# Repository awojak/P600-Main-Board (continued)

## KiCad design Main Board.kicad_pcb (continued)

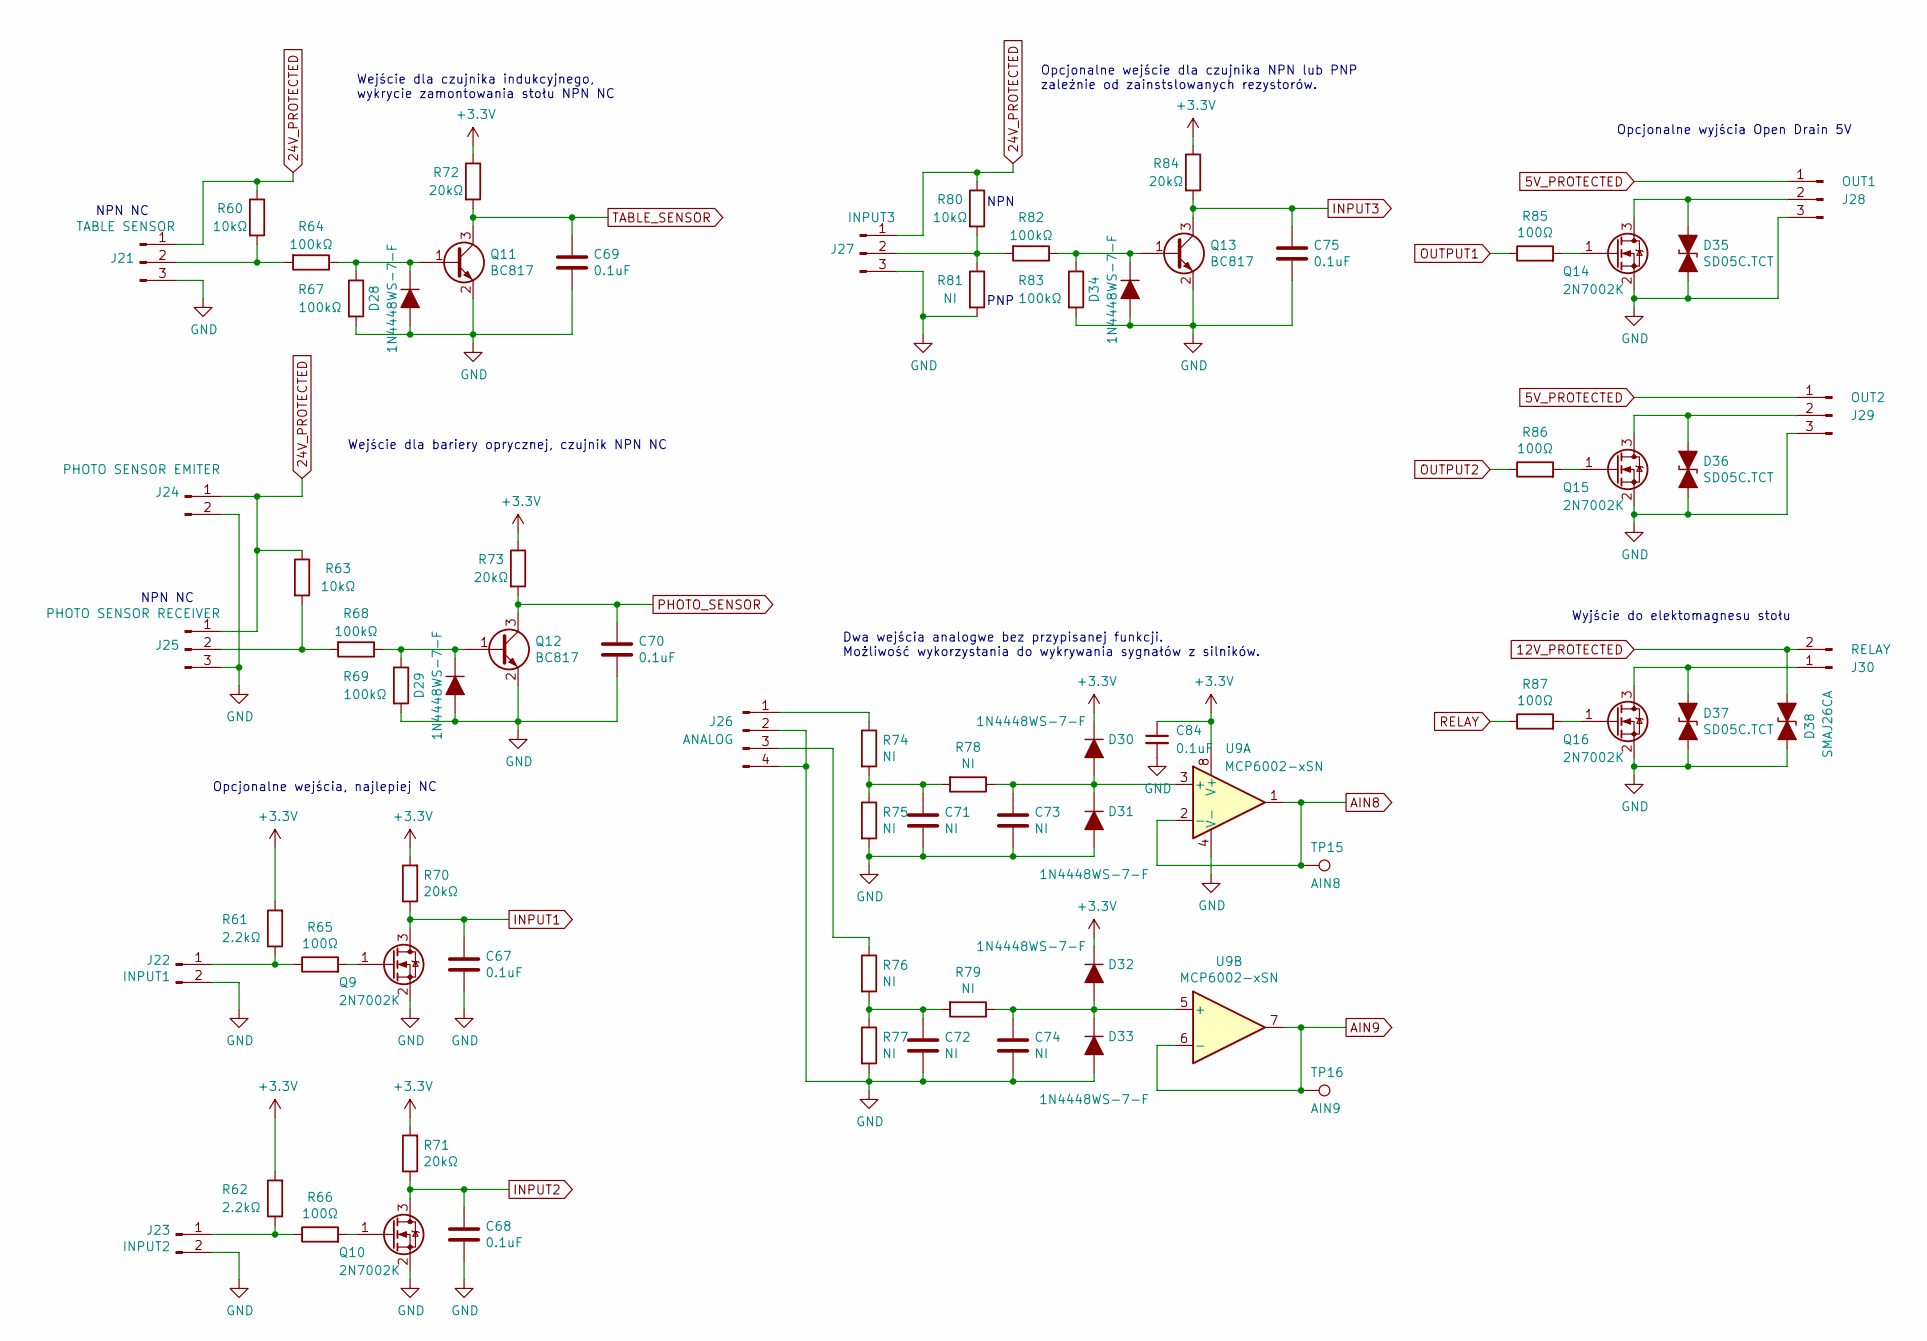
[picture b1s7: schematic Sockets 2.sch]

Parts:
C67, C68, C69, C70, C75: 0.1uF; C_0603_1608Metric
C71, C72, C73, C74: NI; C_0603_1608Metric
C84: 0.1uF; C_0603_1608Metric; Tolerancja 10%
D28, D29, D30, D31, D32, D33, D34: 1N4448WS-7-F; D_SOD-323
D35, D36, D37: SD05C.TCT; D_SOD-323
D38: SMAJ26CA; D_SMA
J21: TABLE SENSOR; JST_PH_B3B-PH-K_1x03_P2.00mm_Vertical
J22: INPUT1; JST_PH_B2B-PH-K_1x02_P2.00mm_Vertical
J23: INPUT2; JST_PH_B2B-PH-K_1x02_P2.00mm_Vertical
J24: PHOTO SENSOR EMITER; JST_PH_B2B-PH-K_1x02_P2.00mm_Vertical
J25: PHOTO SENSOR RECEIVER; JST_PH_B3B-PH-K_1x03_P2.00mm_Vertical
J26: ANALOG; JST_PH_B4B-PH-K_1x04_P2.00mm_Vertical
J27: INPUT3; JST_PH_B3B-PH-K_1x03_P2.00mm_Vertical
J28: OUT1; JST_PH_B3B-PH-K_1x03_P2.00mm_Vertical
J29: OUT2; JST_PH_B3B-PH-K_1x03_P2.00mm_Vertical
J30: RELAY; JST_PH_B2B-PH-K_1x02_P2.00mm_Vertical
Q9, Q10, Q14, Q15, Q16: 2N7002K; SOT-23
Q11, Q12, Q13: BC817; SOT-23
R60, R63, R80: 10kΩ; R_0603_1608Metric
R61, R62: 2.2kΩ; R_0603_1608Metric
R64, R67, R68, R69, R82, R83: 100kΩ; R_0603_1608Metric
R65, R66, R85, R86, R87: 100Ω; R_0603_1608Metric
R70, R71, R72, R73, R84: 20kΩ; R_0603_1608Metric
R74, R75, R76, R77, R78, R79, R81: NI; R_0603_1608Metric
TP15: AIN8; TestPoint_Pad_D1.5mm
TP16: AIN9; TestPoint_Pad_D1.5mm
U9: MCP6002-xSN; SOIC-8_3.9x4.9mm_P1.27mm

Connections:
5V_PROTECTED: J28.1, J29.1; also elsewhere on the board
12V_PROTECTED: D38.1 (A1), J30.2; also elsewhere on the board
24V_PROTECTED: J21.1, J24.1, J25.1, J27.1, R60.1, R63.1, R80.1; also elsewhere on the board
+3V3: C84.1, D30.1 (K), D32.1 (K), R61.2, R62.2, R70.2, R71.2, R72.1, R73.1, R84.1, U9.8 (V+); also elsewhere on the board
AIN8: TP15.1, U9.1, U9.2 (-); also elsewhere on the board
AIN9: TP16.1, U9.6 (-), U9.7; also elsewhere on the board
GND: C67.2, C68.2, C69.2, C70.2, C71.2, C72.2, C73.2, C74.2, C75.2, C84.2, D28.2 (A), D29.2 (A), D31.2 (A), D33.2 (A), D34.2 (A), D35.2 (A2), D36.2 (A2), D37.2 (A2), D38.2 (A2), J21.3, J22.2, J23.2, J24.2, J25.3, J26.2, J26.4, J27.3, J28.3, J29.3, Q9.2 (S), Q10.2 (S), Q11.2 (E), Q12.2 (E), Q13.2 (E), Q14.2 (S), Q15.2 (S), Q16.2 (S), R67.2, R69.2, R75.2, R77.2, R81.2, R83.2, U9.4 (V-); also elsewhere on the board
INPUT1: C67.1, Q9.3 (D), R70.1; also elsewhere on the board
INPUT2: C68.1, Q10.3 (D), R71.1; also elsewhere on the board
INPUT3: C75.1, Q13.3 (C), R84.2; also elsewhere on the board
unnamed: C71.1, R74.2, R75.1, R78.2
unnamed: C72.1, R76.2, R77.1, R79.2
unnamed: C73.1, D30.2 (A), D31.1 (K), R78.1, U9.3 (+)
unnamed: C74.1, D32.2 (A), D33.1 (K), R79.1, U9.5 (+)
unnamed: D28.1 (K), Q11.1 (B), R64.1, R67.1
unnamed: D29.1 (K), Q12.1 (B), R68.1, R69.1
unnamed: D34.1 (K), Q13.1 (B), R82.1, R83.1
unnamed: D35.1 (A1), J28.2, Q14.3 (D)
unnamed: D36.1 (A1), J29.2, Q15.3 (D)
unnamed: D37.1 (A1), J30.1, Q16.3 (D)
unnamed: J21.2, R60.2, R64.2
unnamed: J22.1, R61.1, R65.1
unnamed: J23.1, R62.1, R66.1
unnamed: J25.2, R63.2, R68.2
unnamed: J26.1, R74.1
unnamed: J26.3, R76.1
unnamed: J27.2, R80.2, R81.1, R82.2
unnamed: Q9.1 (G), R65.2
unnamed: Q10.1 (G), R66.2
unnamed: Q14.1 (G), R85.2
unnamed: Q15.1 (G), R86.2
unnamed: Q16.1 (G), R87.2
OUTPUT1: R85.1; also elsewhere on the board
OUTPUT2: R86.1; also elsewhere on the board
PHOTO_SENSOR: C70.1, Q12.3 (C), R73.2; also elsewhere on the board
RELAY: R87.1; also elsewhere on the board
TABLE_SENSOR: C69.1, Q11.3 (C), R72.2; also elsewhere on the board

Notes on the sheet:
NPN NC
NPN
PNP
Dwa wejścia analogwe bez przypisanej funkcji. Możliwość wykorzystania do wykrywania sygnałów z silników.
Wejście dla bariery oprycznej, czujnik NPN NC
Wejście dla czujnika indukcyjnego, wykrycie zamontowania stołu NPN NC
Opcjonalne wejście dla czujnika NPN lub PNP zależnie od zainstslowanych rezystorów.
Opcjonalne wyjścia Open Drain 5V
Wyjście do elektomagnesu stołu
Opcjonalne wejścia, najlepiej NC

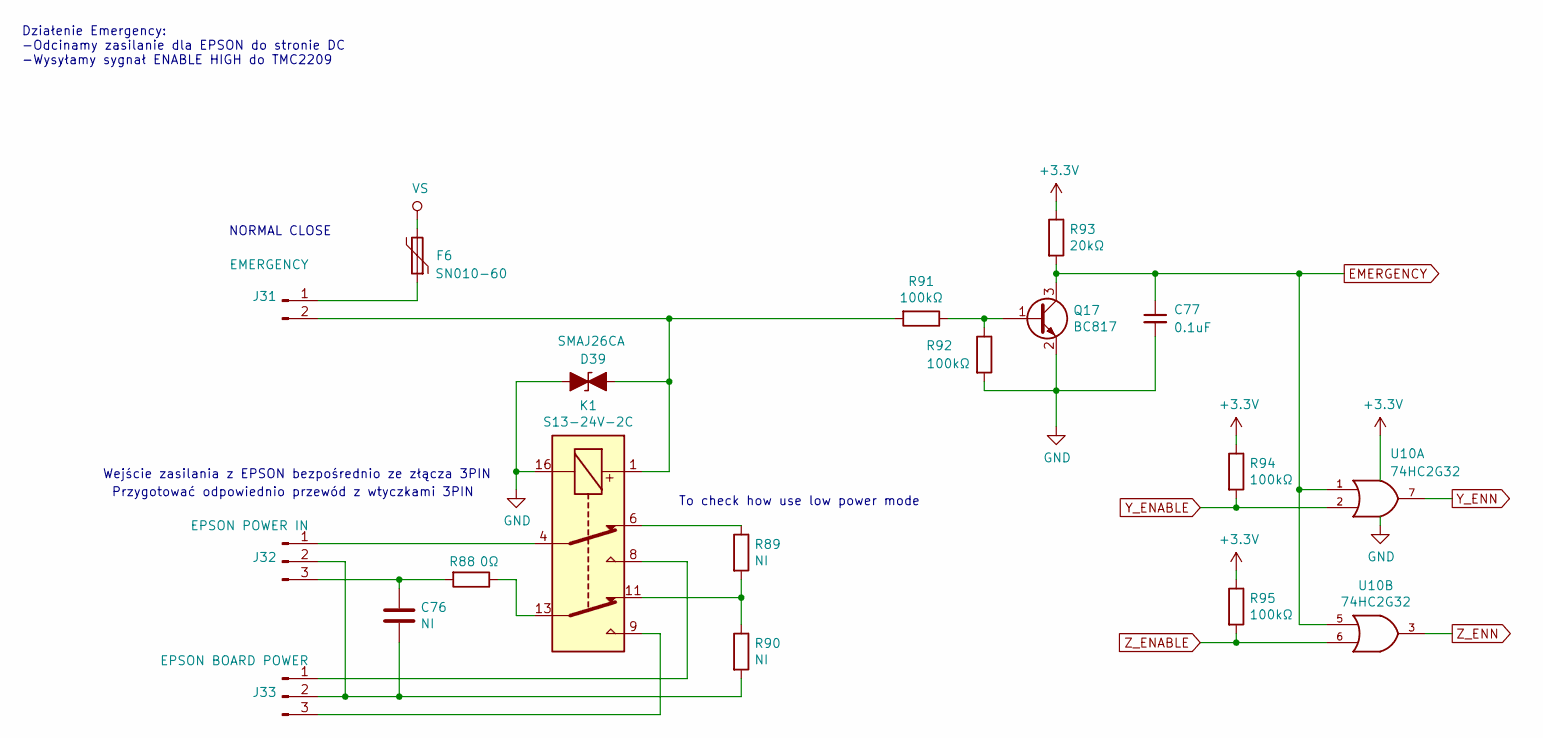
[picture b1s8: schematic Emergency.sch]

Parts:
C76: NI; C_0805_2012Metric
C77: 0.1uF; C_0603_1608Metric
D39: SMAJ26CA; D_SMA
F6: SN010-60; Fuse_1206_3216Metric
J31: EMERGENCY; JST_PH_B2B-PH-K_1x02_P2.00mm_Vertical
J32: EPSON POWER IN; JST_PH_B3B-PH-K_1x03_P2.00mm_Vertical
J33: EPSON BOARD POWER; JST_PH_B3B-PH-K_1x03_P2.00mm_Vertical
K1: S13-24V-2C; Relay_DPDT_Omron_G5V-2
Q17: BC817; SOT-23
R88: 0Ω; R_0805_2012Metric
R89, R90: NI; R_0805_2012Metric
R91, R92, R94, R95: 100kΩ; R_0603_1608Metric
R93: 20kΩ; R_0603_1608Metric
U10: 74HC2G32; VSSOP-8_2.3x2mm_P0.5mm

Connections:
+3V3: R93.1, R94.1, R95.1, U10.8 (VCC); also elsewhere on the board
EMERGENCY: C77.1, Q17.3 (C), R93.2, U10.1, U10.5; also elsewhere on the board
GND: C77.2, D39.1 (A1), K1.16, Q17.2 (E), R92.2, U10.4 (GND); also elsewhere on the board
unnamed: C76.1, J32.3, R88.2
unnamed: C76.2, J32.2, J33.2, R90.2
unnamed: D39.2 (A2), J31.2, K1.1, R91.2
unnamed: F6.1, J31.1
unnamed: J32.1, K1.4
unnamed: J33.1, K1.8
unnamed: J33.3, K1.9
unnamed: K1.6, R89.1
unnamed: K1.11, R89.2, R90.1
unnamed: K1.13, R88.1
unnamed: Q17.1 (B), R91.1, R92.1
VS: F6.2; also elsewhere on the board
Y_ENABLE: R94.2, U10.2; also elsewhere on the board
Y_ENN: U10.7; also elsewhere on the board
Z_ENABLE: R95.2, U10.6; also elsewhere on the board
Z_ENN: U10.3; also elsewhere on the board

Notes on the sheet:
Działenie Emergency: -Odcinamy zasilanie dla EPSON do stronie DC -Wysyłamy sygnał ENABLE HIGH do TMC2209
Wejście zasilania z EPSON bezpośrednio ze złącza 3PIN
Przygotować odpowiednio przewód z wtyczkami 3PIN
NORMAL CLOSE
To check how use low power mode

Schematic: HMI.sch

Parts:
C78: 0.1uF; C_0603_1608Metric; Tolerancja 10%
C79, C80, C81, C82: 0.1uF; C_0603_1608Metric
C85, C86: 0.01uF; C_0603_1608Metric
D40, D41, D42, D43: SKL32; D_SOD-123F
D44, D45: SD05C.TCT; D_SOD-323
F7: SR050; Fuse_0805_2012Metric
J34: Display; JST_PH_B10B-PH-K_1x10_P2.00mm_Vertical
J35: SPI Interface; JST_PH_B5B-PH-K_1x05_P2.00mm_Vertical
J36: I2C Interface; JST_PH_B4B-PH-K_1x04_P2.00mm_Vertical
J37: LED4; JST_PH_B2B-PH-K_1x02_P2.00mm_Vertical
J38: LED3; JST_PH_B2B-PH-K_1x02_P2.00mm_Vertical
J39: Key 3; JST_PH_B2B-PH-K_1x02_P2.00mm_Vertical
J40: Key 4; JST_PH_B2B-PH-K_1x02_P2.00mm_Vertical
J41: Key 1; JST_PH_B2B-PH-K_1x02_P2.00mm_Vertical
J42: Key 2; JST_PH_B2B-PH-K_1x02_P2.00mm_Vertical
J43: Encoder; JST_PH_B3B-PH-K_1x03_P2.00mm_Vertical
Q18, Q19: 2N7002K; SOT-23
R47, R100, R101: 330Ω; R_0603_1608Metric
R96, R97: 20Ω; R_0603_1608Metric
R98, R99: 100Ω; R_0603_1608Metric
R102, R103, R104, R105, R106, R107, R108, R109, R117, R118, R119, R120: 10kΩ; R_0603_1608Metric
RN3, RN4: 330Ω; R_Array_Convex_4x0603
U11: 74HC245; TSSOP-20_4.4x6.5mm_P0.65mm

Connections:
3.3V_PROTECTED: J36.1; also elsewhere on the board
+3V3: D40.1 (K), D42.1 (K); also elsewhere on the board
+5V: C78.1, F7.2, R100.2, R101.2, R102.2, R103.2, R104.2, R105.2, R117.2, R118.2, U11.1 (A->B), U11.20 (VCC); also elsewhere on the board
ENC2_A: C85.1, R119.1; also elsewhere on the board
ENC2_B: C86.1, R120.1; also elsewhere on the board
GND: C78.2, C79.2, C80.2, C81.2, C82.2, C85.2, C86.2, D41.2 (A), D43.2 (A), D44.2 (A2), D45.2 (A2), J34.9, J34.10, J35.5, J36.3, J39.2, J40.2, J41.2, J42.2, J43.2, Q18.2 (S), Q19.2 (S), U11.10 (GND), U11.19 (CE); also elsewhere on the board
I2C_SCL: D40.2 (A), D41.1 (K), R97.2; also elsewhere on the board
I2C_SDA: D42.2 (A), D43.1 (K), R96.2; also elsewhere on the board
KEY_1: C81.1, R108.1; also elsewhere on the board
KEY_2: C82.1, R109.1; also elsewhere on the board
KEY_3: C79.1, R106.1; also elsewhere on the board
KEY_4: C80.1, R107.1; also elsewhere on the board
LCD_DB4: U11.7 (A5); also elsewhere on the board
LCD_DB5: U11.6 (A4); also elsewhere on the board
LCD_DB6: U11.5 (A3); also elsewhere on the board
LCD_DB7: U11.4 (A2); also elsewhere on the board
LCD_E: U11.3 (A1); also elsewhere on the board
LCD_PWM: U11.8 (A6); also elsewhere on the board
LCD_RS: U11.2 (A0); also elsewhere on the board
LED3: R98.1; also elsewhere on the board
LED4: R99.1; also elsewhere on the board
unnamed: D44.1 (A1), J37.2, Q19.3 (D)
unnamed: D45.1 (A1), J38.2, Q18.3 (D)
unnamed: F7.1, J34.1, J35.1
unnamed: J34.2, RN3.4 (R4.1)
unnamed: J34.3, RN3.3 (R3.1)
unnamed: J34.4, RN3.2 (R2.1)
unnamed: J34.5, RN3.1 (R1.1)
unnamed: J34.6, RN4.4 (R4.1)
unnamed: J34.7, RN4.3 (R3.1)
unnamed: J34.8, RN4.2 (R2.1)
unnamed: J35.4, R47.2
unnamed: J36.2, R96.1
unnamed: J36.4, R97.1
unnamed: J37.1, R101.1
unnamed: J38.1, R100.1
unnamed: J39.1, R102.1, R106.2
unnamed: J40.1, R103.1, R107.2
unnamed: J41.1, R104.1, R108.2
unnamed: J42.1, R105.1, R109.2
unnamed: J43.1, R117.1, R119.2
unnamed: J43.3, R118.1, R120.2
unnamed: Q18.1 (G), R98.2
unnamed: Q19.1 (G), R99.2
unnamed: RN3.5 (R4.2), U11.18 (B0)
unnamed: RN3.6 (R3.2), U11.17 (B1)
unnamed: RN3.7 (R2.2), U11.16 (B2)
unnamed: RN3.8 (R1.2), U11.15 (B3)
unnamed: RN4.5 (R4.2), U11.14 (B4)
unnamed: RN4.6 (R3.2), U11.13 (B5)
unnamed: RN4.7 (R2.2), U11.12 (B6)
SPI_MISO: R47.1; also elsewhere on the board
SPI_MOSI_BUF: J35.2; also elsewhere on the board
SPI_SCLK_BUF: J35.3; also elsewhere on the board

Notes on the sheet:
Wyjście dla Wyświetlacza HD44780
Buffered outputs signals
Złącza JST PH
Wejścia dla klawiszy funkcyjnych, nie przypisane
RC Debounce
Check if switching is fast enought
ESD
Wyjście I2C do potencjanych czujników
Wyjście SPI do modułu komunikacji z użytkownikiem
Wyjście OD dla opcjonalnych LED
Rotary encoder input

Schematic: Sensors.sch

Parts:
C83, C95: 0.1uF; C_0603_1608Metric; Tolerancja 10%
Q20, Q21: 2N7002K; SOT-23
R1: 10kΩ; R_0603_1608Metric
R110, R112: 2.2kΩ; R_0603_1608Metric
R111: 0Ω; R_0603_1608Metric
R113, R114: 100Ω; R_0603_1608Metric
R115, R116: 20kΩ; R_0603_1608Metric
U12: SHTC3; DFN-4-1EP_2x2mm_P1mm_EP0.7x1.6mm
U13: M24C02-WDW; TSSOP-8_4.4x3mm_P0.65mm

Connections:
5V_DETECT: Q20.3 (D), R115.1; also elsewhere on the board
12V_DETECT: Q21.3 (D), R116.1; also elsewhere on the board
+3V3: C83.1, C95.2, R1.1, R110.1, R112.1, R115.2, R116.2, U12.1 (VDD), U13.8 (VCC); also elsewhere on the board
+5V: R113.1; also elsewhere on the board
+12V: R114.1; also elsewhere on the board
EEPROM_P: R1.2, U13.7 (~WC); also elsewhere on the board
GND: C83.2, C95.1, Q20.2 (S), Q21.2 (S), U12.4 (VSS), U13.4 (VSS); also elsewhere on the board
I2C_SCL: R112.2, U12.2 (SCL), U13.6 (SCL); also elsewhere on the board
I2C_SDA: R110.2, R111.1, U13.5 (SDA); also elsewhere on the board
unnamed: Q20.1 (G), R113.2
unnamed: Q21.1 (G), R114.2
unnamed: R111.2, U12.3 (SDA)

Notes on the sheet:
Wykrycie napięć z przetwornic 5V i 12V
Czujnik wilgotności i temperatury
Rezystor do odłączenia układy gdy chcielibyśmy podłączyć taki sam na zewnętrznych I2C. I2C z wyjściem jest dzielone z tym czujnikiem

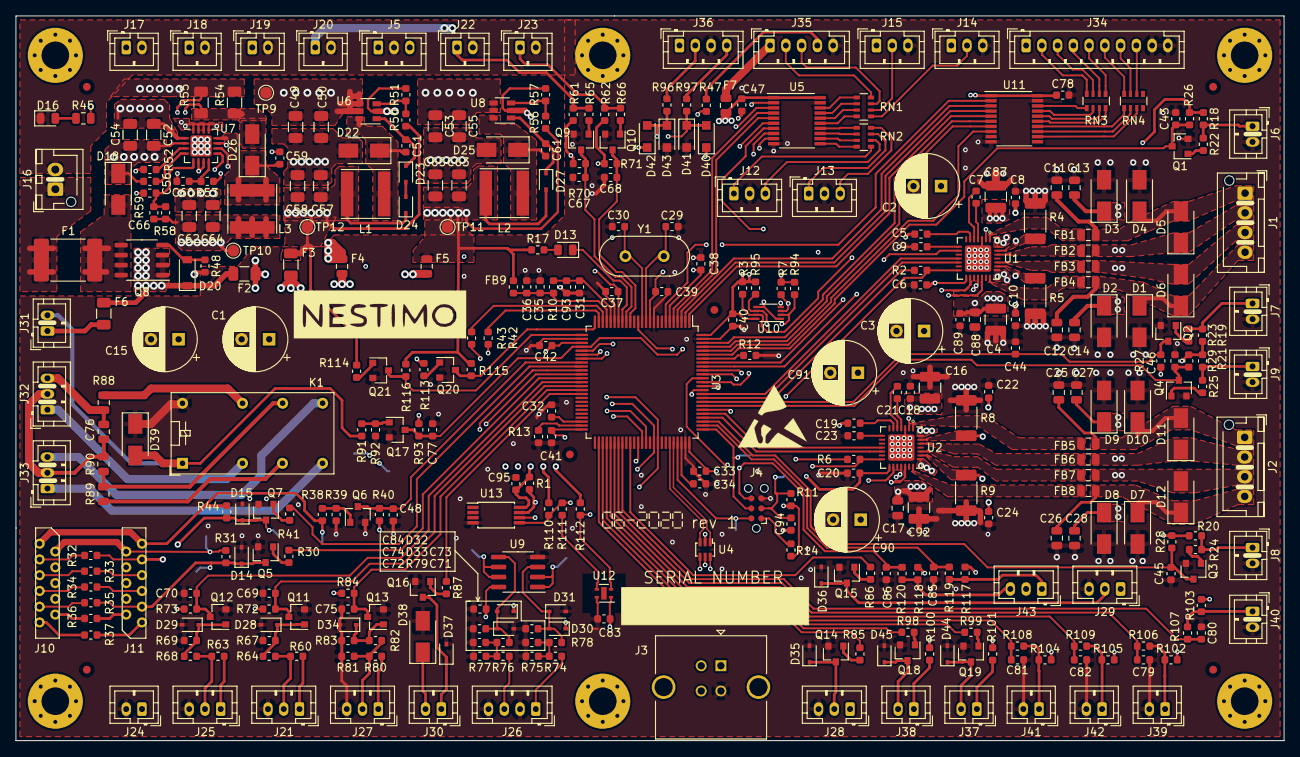
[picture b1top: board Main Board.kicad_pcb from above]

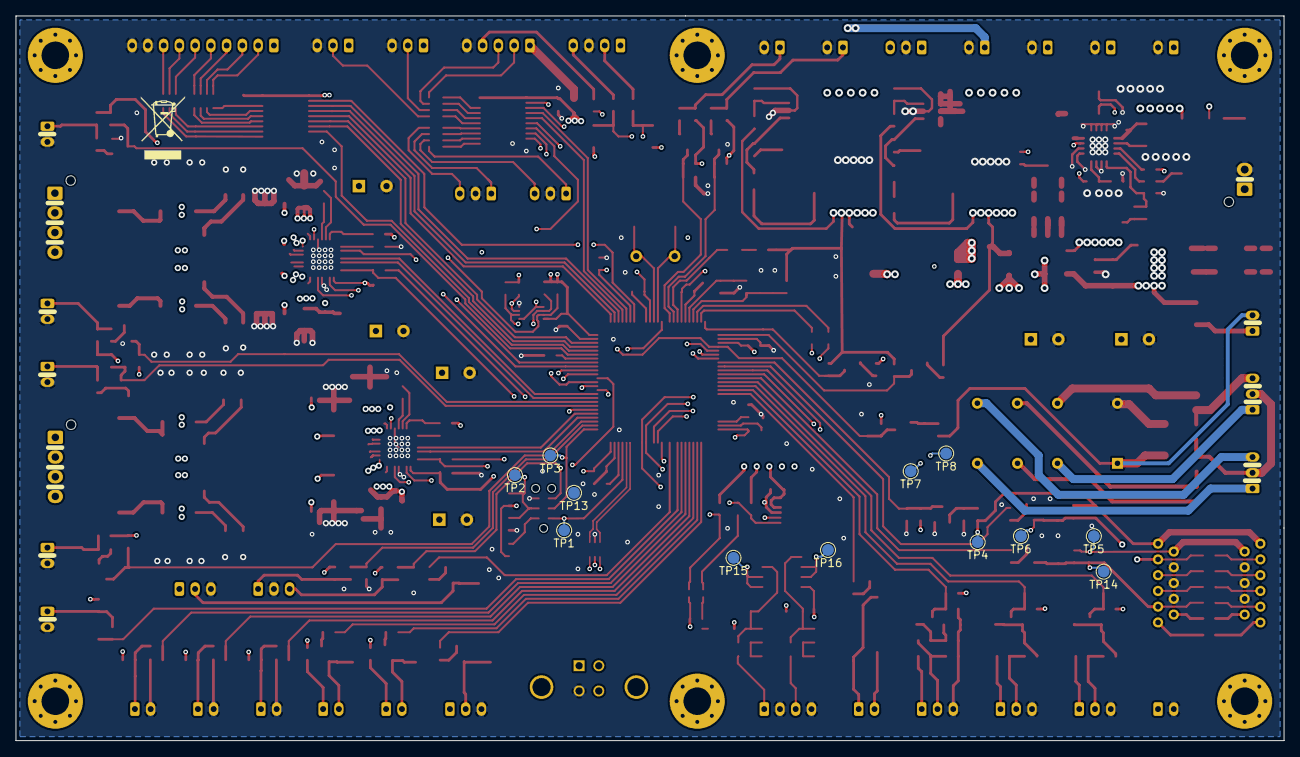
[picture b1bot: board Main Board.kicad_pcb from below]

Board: 4 copper layers, 161.0 x 92.0 mm, 383 parts (12 on the bottom side), 241 nets.

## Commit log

2019-12-04 Init Commit
2019-12-20 Added stm32f401
2019-12-22 Finished TMC2209 schematic for Y and Z motor, added BOM
2020-01-02 Added Power.sch and update BOM
2020-01-02 Finished Power Managment
2020-01-03 Added Input Limit Switch
2020-01-05 Finished Emergency Circuit
2020-01-06 Added Polyfuses and replace diodes
2020-01-06 Added USB B socket with ESD filter
2020-01-07 Added SWD and Debug out
2020-01-07 Improve schematics add new elements
2020-01-08 Numbering and finishing the schematic
2020-01-08 Shematic almost finished, BOM in KiCad 3/4 finished
2020-01-09 BOM in KiCad almost finished, genereated NETLIST, create PCB
2020-01-09 Generated BOM
2020-01-09 Improve Emergency, Added TVS diodes
2020-01-10 Update USBUF02W6
2020-01-10 Added 12V regulator, aditional input, outputs, improved inputs ESD
2020-01-11 Added analog input
2020-01-11 Improve ESD Protection for TMC2209, Fuses. Schematic ready v1
2020-01-11 Dodano brakujący footprint dla R1
2020-01-12 Routing of the power supplies are finished
2020-01-12 Rozmieszczenie elementów, trasowanie ścieżek, etap 2/4
2020-01-13 Added DJNR6045 3D package
2020-01-13 Update Crystal footprint and inductor 3D package on PCB
2020-01-13 Added JST FMN, USB Type B, JST XH 3d package. Update PCB
2020-01-13 Change SWD IDC connector to TC2030
2020-01-13 Change USB Horizontal to Vertical
2020-01-13 Added git ignore, updated part info for USB socket
2020-01-13 Start ignoring .sch-bak files
2020-01-13 Start ignoring .kicad_pcb-bak
2020-01-14 Added rotary encoder input
2020-01-14 Modify pin attribute, routing keys input
2020-01-15 Routing emergnency, photo barier, relay, voltage detect, analog, footprint improvment
2020-01-16 Start TMC routing
2020-01-16 TMC2209 routing step 2/3
2020-01-17 Routing almost finished
2020-01-21 Test points, start power plane routing, little change on schematic
2020-01-21 +5V Power plane routing
2020-01-21 Routing PCB finished
2020-01-21 Silk layers finished
2020-01-22 Added Nestimo logo, generated gerber files
2020-01-22 Added 3d packages, improved TMC2209 footprint
2020-01-22 Update gerber
2020-01-23 Added EEPROM on schematic
2020-01-24 EEPROM Routing, Updated gerber files
2020-01-24 Update elements value
2020-02-03 Update silk layer, update TMC label, added revision, serial number, generated gerbera
2020-02-18 Updated BOM on schematics
